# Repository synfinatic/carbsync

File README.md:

### CarbSync

While there are some good tools already on the market by companies like
[MotionPro](http://www.motionpro.com/motorcycle/partno/08-0411/) or 
[Morgan Carbtune](http://www.carbtune.com/), they tend to be complicated,
may use fluids which are toxic or spill, and require a complex calibration
sequence for best results.

CarbSync is a simple tool for syncing carberators or throttle bodies which uses
digital vacuum gauges to measure the vacuum on 2 to 4 cylinders.  By using 
solid-state vacuum gauges which require no calibration and have no fluid to leak,
CarbSync is both accurate and easy to use.

### Technical Specs
 * CarbSync has a useful vacuum measurement range of 0 to -7.25 PSI (-50 kPA)
     allowing it to be used with almost any vehicle
 * CarbSync has a LCD for displaying results
 * CarbSync supports 2, 3 or 4 cylinder engines
 * Powered by AA batteries

### Thanks
Special thanks to [Michael Miller](http://www.instructables.com/member/Makuna/)
for his [Arduino Throttle Body Synchronization Sheild](http://www.instructables.com/id/Arduino-Throttle-Body-Syncronization-Shield/?ALLSTEPS)
idea which gave me the idea for this project.

### License
CarbSync is licensed under the [GPLv3](http://www.gnu.org/licenses/gpl.html)

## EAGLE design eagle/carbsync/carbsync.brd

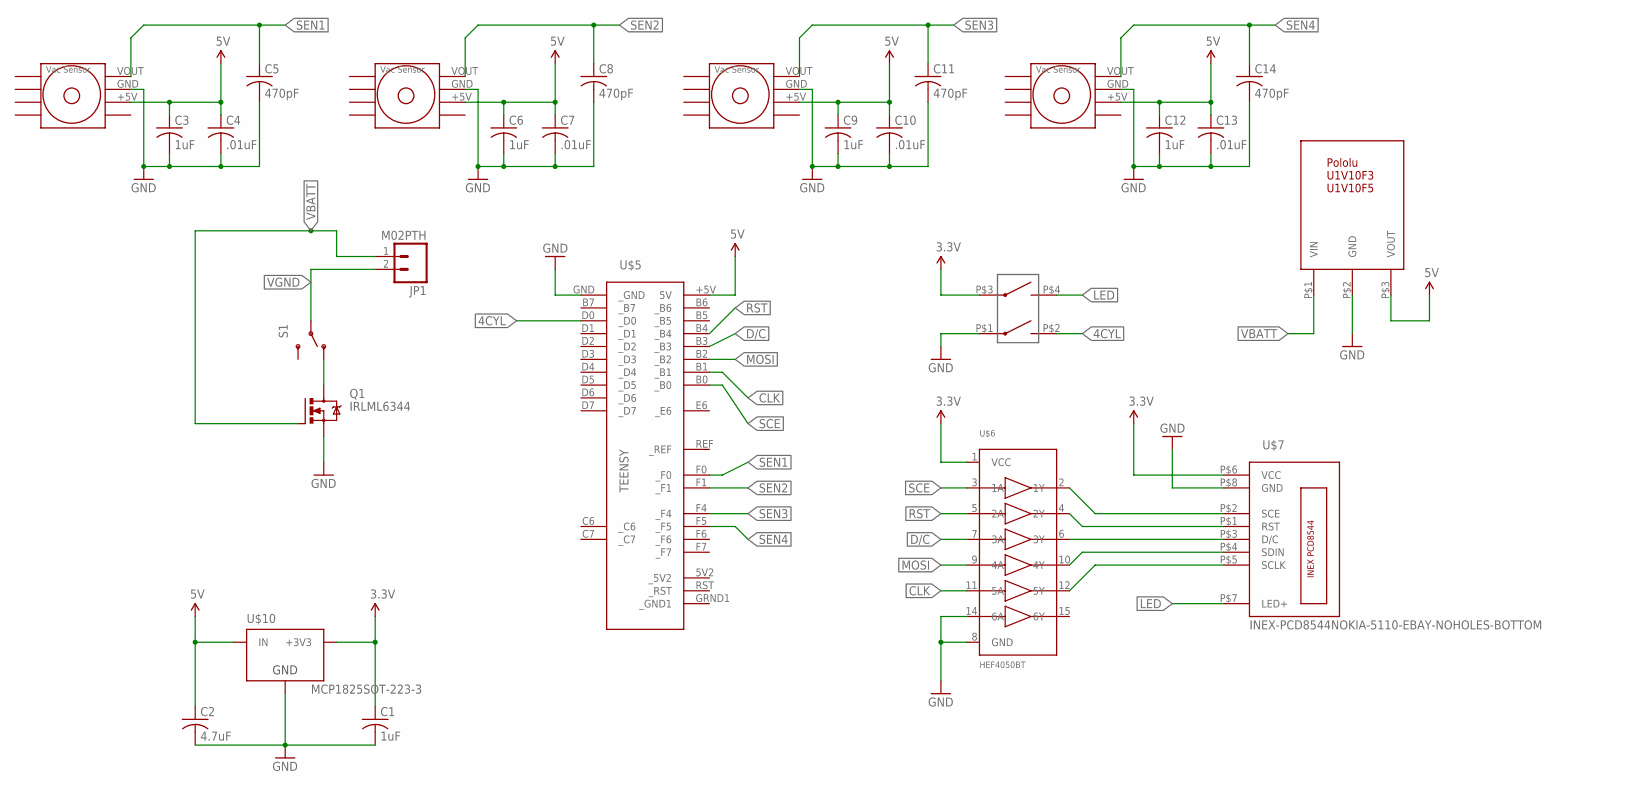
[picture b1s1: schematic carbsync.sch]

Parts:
C1, C3, C6, C9, C12: 1uF; C0805
C2: 4.7uF; C0805
C4, C7, C10, C13: .01uF; C0805
C5, C8, C11, C14: 470pF; C0603
JP1: M02PTH; 1X02
Q1: IRLML6344; SOT23
S1: SWITCH-SPDT; CWI286-SPDT-NOTABS
U$1, U$2, U$3, U$4: MPXV5050V
U$5: TEENSY
U$6: HEF4050BT; SOIC16
U$7: INEX-PCD8544NOKIA-5110-EBAY-NOHOLES-BOTTOM; NOKIA-5110-EBAY-NOHOLES
U$8: POLOLU-DC-3PINU1V10F5-5V-DC-UP; POLOLU-DC-3PIN
U$9: CT-219-X-MST; CT219-2-MST
U$10: MCP1825SOT-223-3; SOT-223

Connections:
3.3V: C1.1, U$6.1 (VCC), U$7.P$6 (VCC), U$9.P$3, U$10.3 (+3V3)
4CYL: U$5.D0 (_D0), U$9.P$2
5V: C2.1, C3.1, C4.1, C6.1, C7.1, C9.1, C10.1, C12.1, C13.1, U$1.+5V (5V), U$2.+5V (5V), U$3.+5V (5V), U$4.+5V (5V), U$5.+5V (5V), U$8.P$3 (VOUT), U$10.1 (IN)
CLK: U$5.B1 (_B1), U$6.11 (5A)
D/C: U$5.B3 (_B3), U$6.7 (3A)
GND: C1.2, C2.2, C3.2, C4.2, C5.2, C6.2, C7.2, C8.2, C9.2, C10.2, C11.2, C12.2, C13.2, C14.2, Q1.2 (S), U$1.GND, U$2.GND, U$3.GND, U$4.GND, U$5.GND (_GND), U$6.8 (GND), U$6.14 (6A), U$7.P$8 (GND), U$8.P$2 (GND), U$9.P$1, U$10.2 (GND), U$10.4 (GND)
LED: U$7.P$7 (LED+), U$9.P$4
MOSI: U$5.B2 (_B2), U$6.9 (4A)
unnamed: U$6.2 (1Y), U$7.P$2 (SCE)
unnamed: U$6.4 (2Y), U$7.P$1 (RST)
unnamed: U$6.6 (3Y), U$7.P$3 (D/C)
unnamed: U$6.10 (4Y), U$7.P$4 (SDIN)
unnamed: U$6.12 (5Y), U$7.P$5 (SCLK)
unnamed: Q1.3 (D), S1.P$1 (O)
RST: U$5.B4 (_B4), U$6.5 (2A)
SCE: U$5.B0 (_B0), U$6.3 (1A)
SEN1: C5.1, U$1.VOUT, U$5.F0 (_F0)
SEN2: C8.1, U$2.VOUT, U$5.F1 (_F1)
SEN3: C11.1, U$3.VOUT, U$5.F4 (_F4)
SEN4: C14.1, U$4.VOUT, U$5.F5 (_F5)
VBATT: JP1.1, Q1.1 (G), U$8.P$1 (VIN)
VGND: JP1.2, S1.P$2

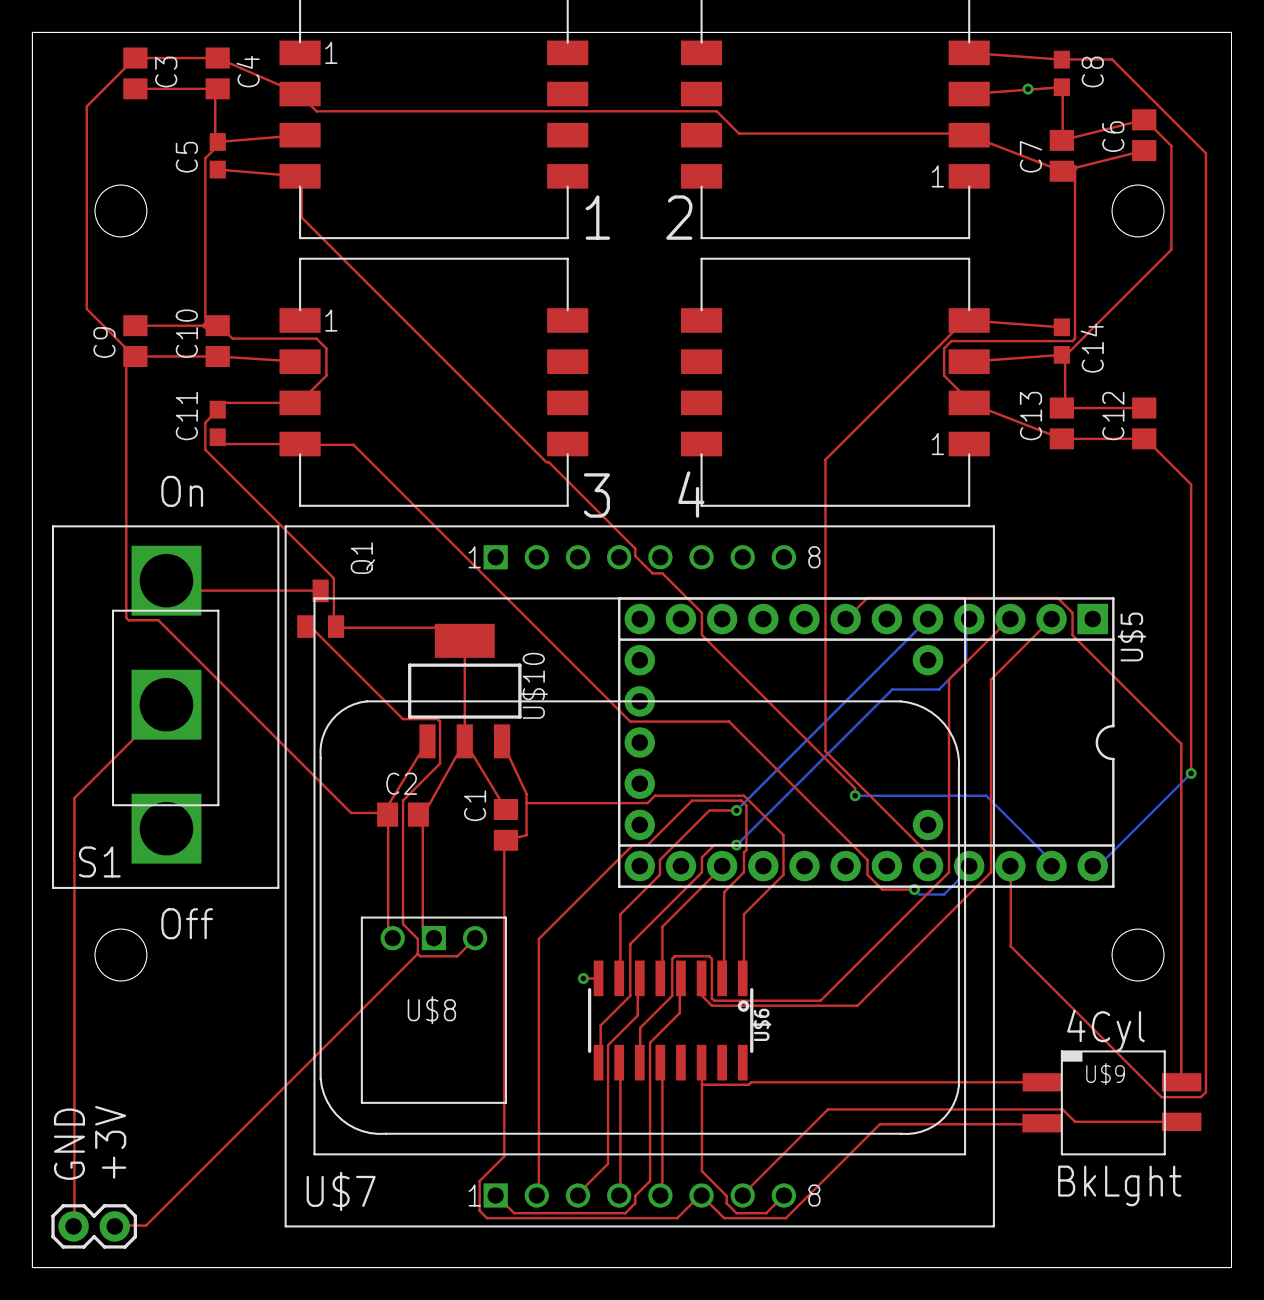
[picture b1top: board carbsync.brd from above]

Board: 2 copper layers, 74.0 x 76.2 mm, 27 parts (0 on the bottom side), 22 nets.

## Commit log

2015-02-11 start work on writing real code. Nothing yet works
2015-03-22 first pass at designing a board. Untested/verified
2015-03-24 update & shrink board a little
    Still uses a MOSFET for reverse voltage protection,
    but I'm pretty sure it won't work.
2015-03-24 remove mosfet, switch to 2-DIP instead of jumpers
2015-03-28 basic 3.5x2.5" board design
2015-04-02 clean up board and fix the level shifter
    Waiting on part order to check footprints & do power switch
2015-04-02 redesign PCB around http://www.hammondmfg.com/pdf/1553D_BAT.pdf
    still need to find a power switch which will work correctly
2015-04-03 remove carbsync.pro & eagle.epf
2015-04-25 v1.0 of PCB done and ordered
2015-04-25 Small readme changes

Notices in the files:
parts and their libraries:
microbuilder: This work is placed in the public domain, and may be freely used for commercial and non-commercial work with the following conditions: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
SparkFun-Connectors: Licensing: Creative Commons ShareAlike 4.0 International - https://creativecommons.org/licenses/by-sa/4.0
